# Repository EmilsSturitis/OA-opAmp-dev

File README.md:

# OA-opAmp-dev

 Dev board for OPA2333 with 10 different op amp circuits
 
 Including:
  Non-inverting
  Invering
  Sallen Key filter
  Single to Diff 
  uttt

design has not been tested.

Circuits have been based on the:
https://www.ti.com/lit/ug/sbou193/sbou193.pdf?ts=1656355367396&ref_url=https%253A%252F%252Fwww.ti.com%252Ftool%252FDUAL-DIYAMP-EVM

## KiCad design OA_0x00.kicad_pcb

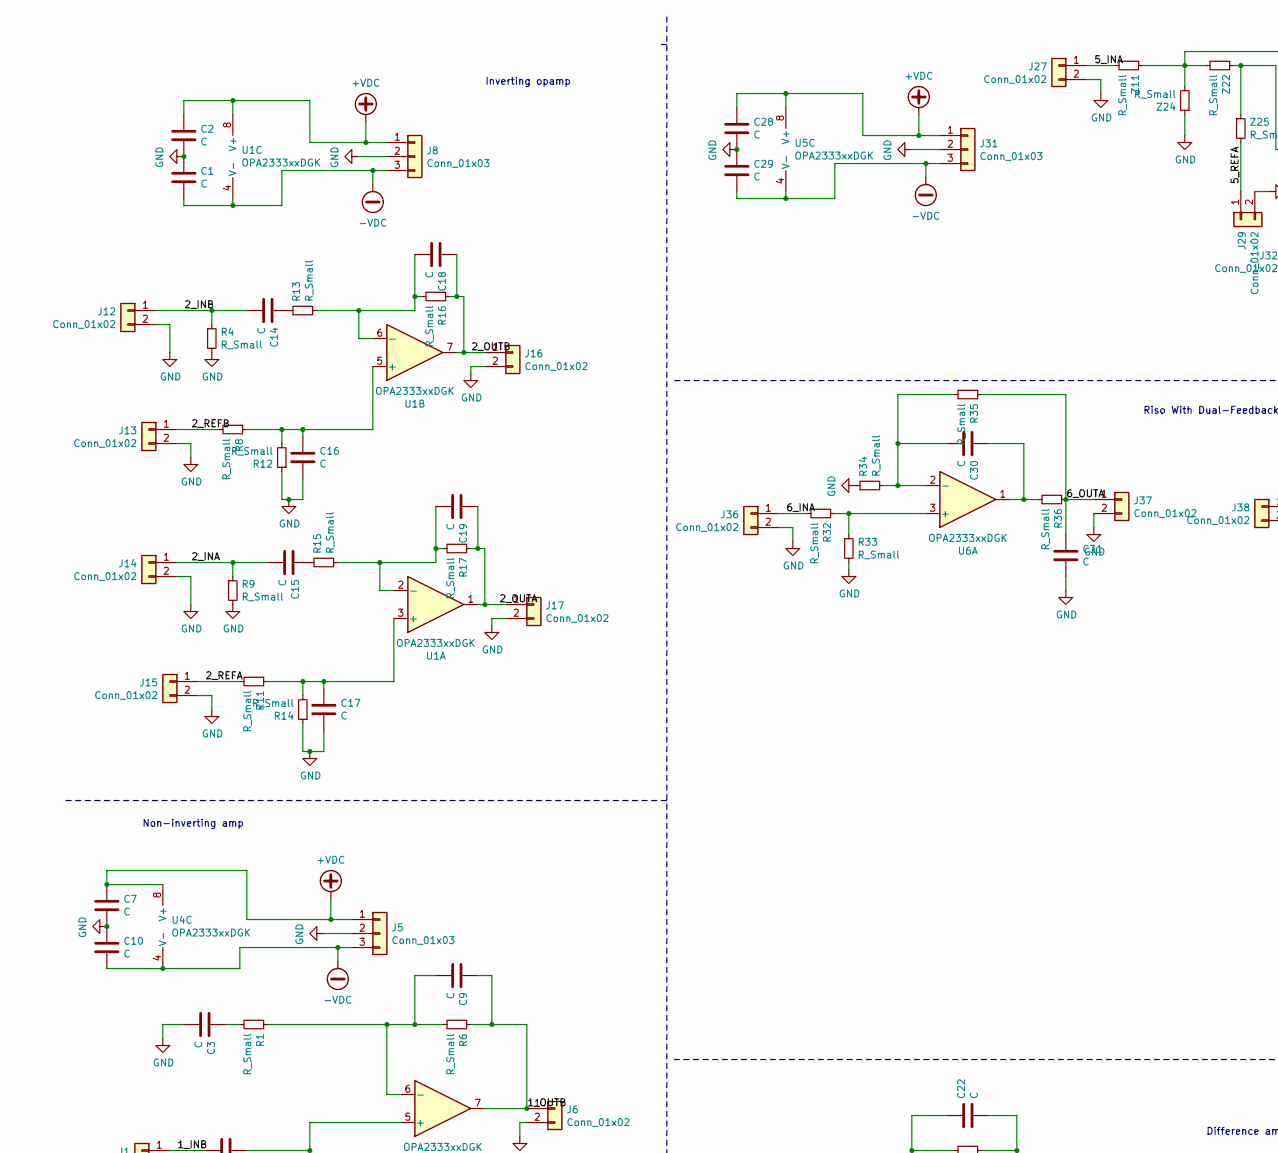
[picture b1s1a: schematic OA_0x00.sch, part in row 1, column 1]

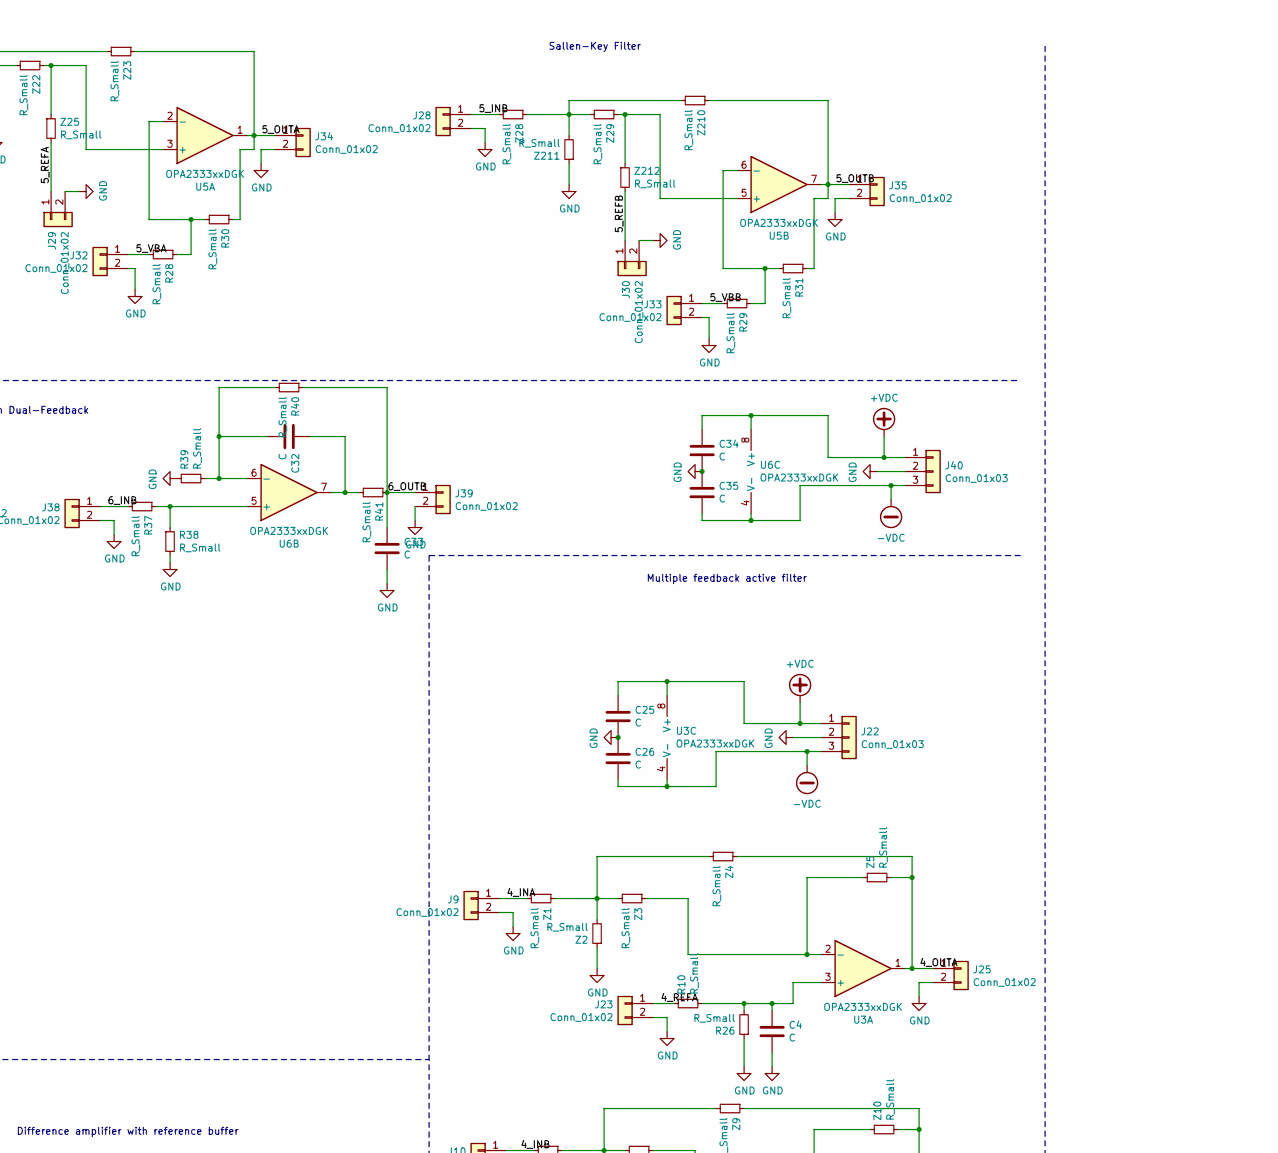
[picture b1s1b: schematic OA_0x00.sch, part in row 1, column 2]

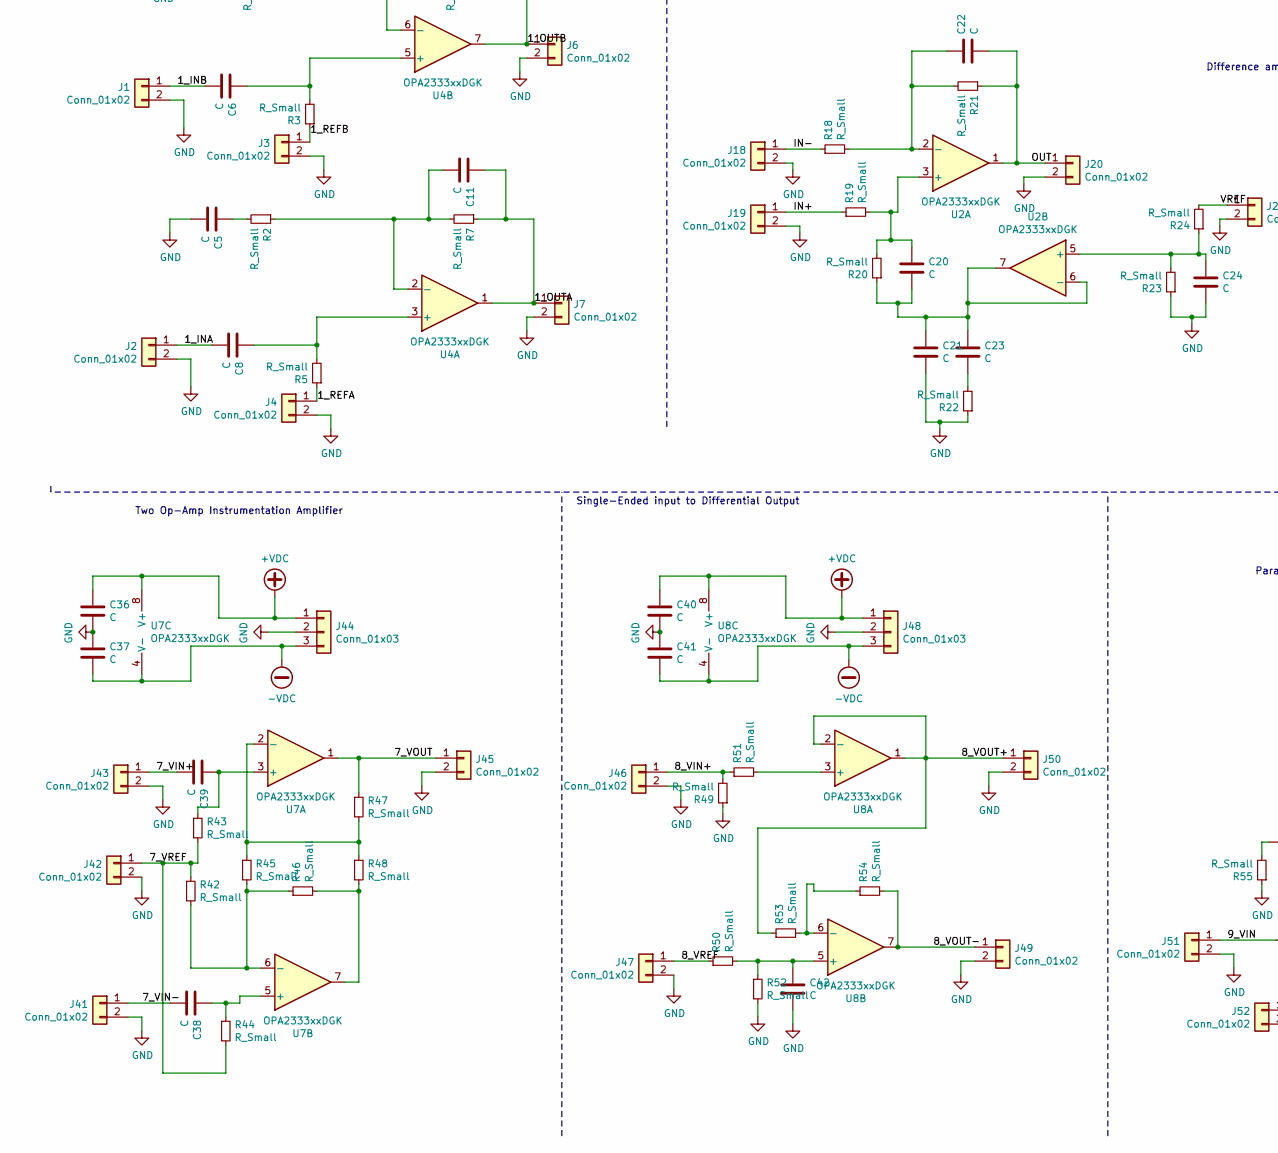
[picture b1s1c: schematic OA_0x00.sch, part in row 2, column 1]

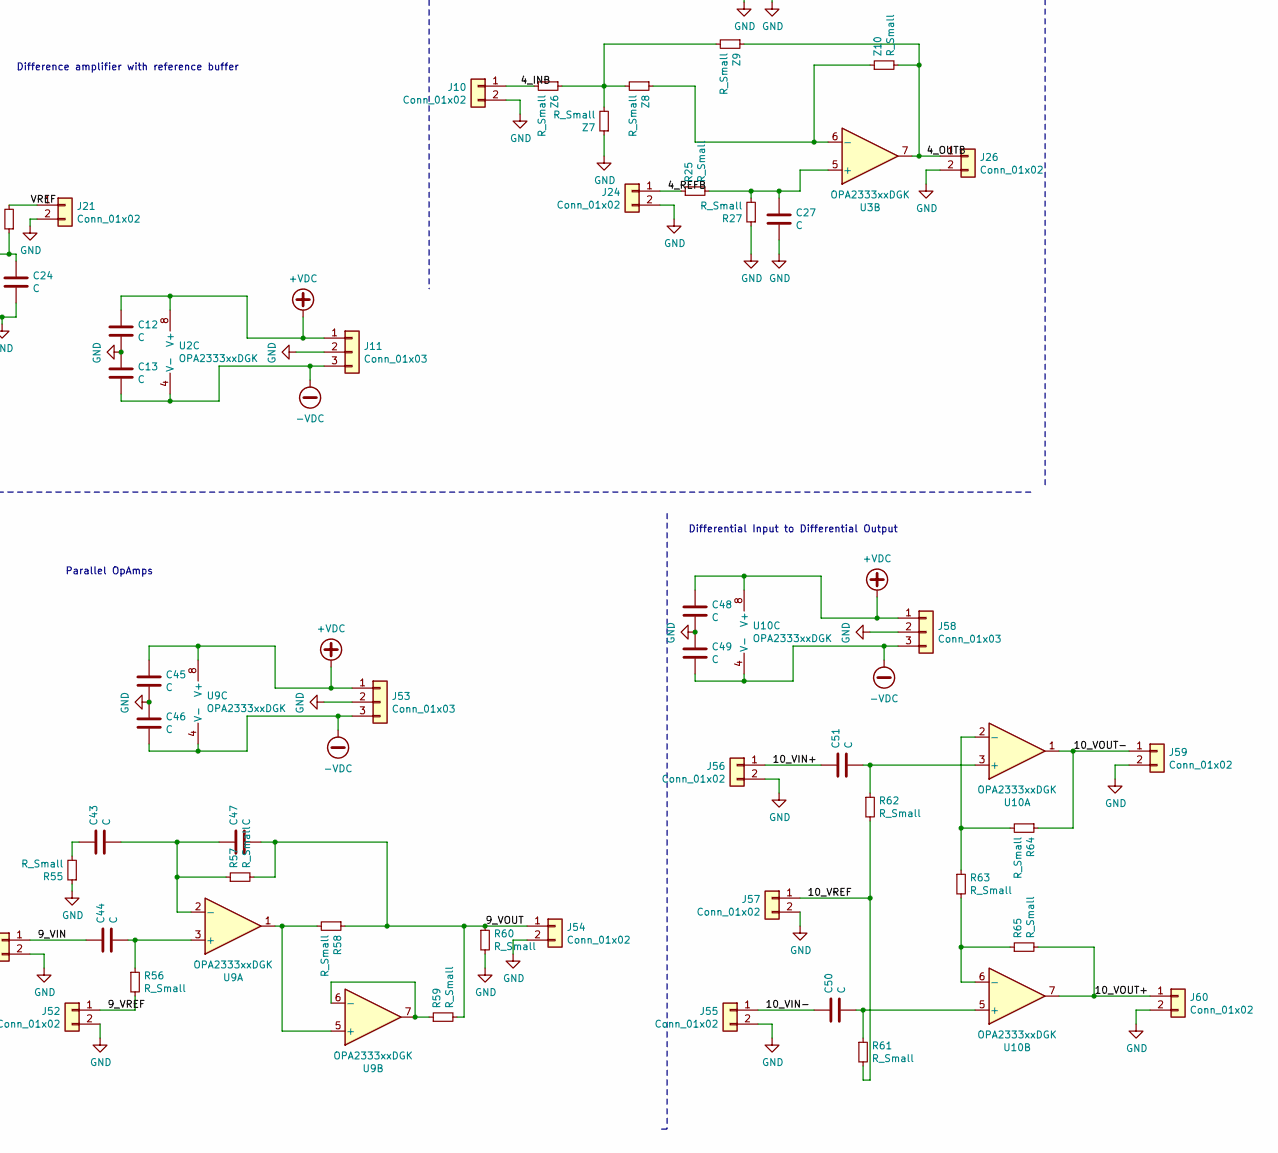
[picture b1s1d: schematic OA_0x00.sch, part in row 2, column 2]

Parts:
C1, C2, C3, C4, C5, C6, C7, C8, C9, C10, C11, C12, C13, C14, C15, C16, C17, C18, C19, C20, C21, C22, C23, C24, C25, C26, C27, C28, C29, C30, C31, C32, C33, C34, C35, C36, C37, C38, C39, C40, C41, C42, C43, C44, C45, C46, C47, C48, C49, C50, C51: C; C_0805_2012Metric_Pad1.18x1.45mm_HandSolder
J1, J2, J3, J4, J6, J7, J9, J10, J12, J13, J14, J15, J16, J17, J18, J19, J20, J21, J23, J24, J25, J26, J27, J28, J29, J30, J32, J33, J34, J35, J36, J37, J38, J39, J41, J42, J43, J45, J46, J47, J49, J50, J51, J52, J54, J55, J56, J57, J59, J60: Conn_01x02; PinHeader_1x02_P2.54mm_Vertical
J5, J8, J11, J22, J31, J40, J44, J48, J53, J58: Conn_01x03; PinHeader_1x03_P2.54mm_Vertical
R1, R2, R3, R4, R5, R6, R7, R8, R9, R10, R11, R12, R13, R14, R15, R16, R17, R18, R19, R20, R21, R22, R23, R24, R25, R26, R27, R28, R29, R30, R31, R32, R33, R34, R35, R36, R37, R38, R39, R40, R41, R42, R43, R44, R45, R46, R47, R48, R49, R50, R51, R52, R53, R54, R55, R56, R57, R58, R59, R60, R61, R62, R63, R64, R65: R_Small; R_0805_2012Metric_Pad1.20x1.40mm_HandSolder
U1, U2, U3, U4, U5, U6, U7, U8, U9, U10: OPA2333xxDGK; VSSOP-8_3.0x3.0mm_P0.65mm
Z1, Z2, Z3, Z4, Z5, Z6, Z7, Z8, Z9, Z10, Z11, Z22, Z23, Z24, Z25, Z28, Z29, Z210, Z211, Z212: R_Small; R_0805_2012Metric_Pad1.20x1.40mm_HandSolder

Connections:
+VDC: C2.1, C7.1, C12.1, C25.1, C28.1, C34.1, C36.1, C40.1, C45.1, C48.1, J5.1, J8.1, J11.1, J22.1, J31.1, J40.1, J44.1, J48.1, J53.1, J58.1, U1.8 (V+), U2.8 (V+), U3.8 (V+), U4.8 (V+), U5.8 (V+), U6.8 (V+), U7.8 (V+), U8.8 (V+), U9.8 (V+), U10.8 (V+)
-VDC: C1.2, C10.2, C13.2, C26.2, C29.2, C35.2, C37.2, C41.2, C46.2, C49.2, J5.3, J8.3, J11.3, J22.3, J31.3, J40.3, J44.3, J48.3, J53.3, J58.3, U1.4 (V-), U2.4 (V-), U3.4 (V-), U4.4 (V-), U5.4 (V-), U6.4 (V-), U7.4 (V-), U8.4 (V-), U9.4 (V-), U10.4 (V-)
/1_INA: C8.2, J2.1
/1_INB: C6.2, J1.1
/1_OUTA: C11.1, J7.1, R7.1, U4.1
/1_OUTB: C9.1, J6.1, R6.1, U4.7
/1_REFA: J4.1, R5.1
/1_REFB: J3.1, R3.1
/2_INA: C15.2, J14.1, R9.1
/2_INB: C14.2, J12.1, R4.1
/2_OUTA: C19.1, J17.1, R17.1, U1.1
/2_OUTB: C18.1, J16.1, R16.1, U1.7
/2_REFA: J15.1, R11.2
/2_REFB: J13.1, R8.2
/4_INA: J9.1, Z1.2
/4_INB: J10.1, Z6.2
/4_OUTA: J25.1, U3.1, Z4.1, Z5.2
/4_OUTB: J26.1, U3.7, Z9.1, Z10.2
/4_REFA: J23.1, R10.1
/4_REFB: J24.1, R25.1
/5_INA: J27.1, Z11.2
/5_INB: J28.1, Z28.2
/5_OUTA: J34.1, R30.1, U5.1, Z23.1
/5_OUTB: J35.1, R31.1, U5.7, Z210.1
/5_REFA: J29.1, Z25.2
/5_REFB: J30.1, Z212.2
/5_VBA: J32.1, R28.2
/5_VBB: J33.1, R29.2
/6_INA: J36.1, R32.2
/6_INB: J38.1, R37.2
/6_OUTA: C31.1, J37.1, R35.1, R36.1
/6_OUTB: C33.1, J39.1, R40.1, R41.1
/7_VIN+: C39.2, J43.1
/7_VIN-: C38.2, J41.1
/7_VOUT: J45.1, R47.1, U7.1
/7_VREF: J42.1, R42.1, R43.2, R44.2
/8_VIN+: J46.1, R49.2, R51.1
/8_VOUT+: J50.1, R53.1, U8.1, U8.2 (-)
/8_VOUT-: J49.1, R54.2, U8.7
/8_VREF: J47.1, R50.1
/9_VIN: C44.1, J51.1
/9_VOUT: C47.2, J54.1, R57.2, R58.1, R59.2, R60.1
/9_VREF: J52.1, R56.2
/10_VIN+: C51.1, J56.1
/10_VIN-: C50.1, J55.1
/10_VOUT+: J60.1, R65.2, U10.7
/10_VOUT-: J59.1, R64.1, U10.1
/10_VREF: J57.1, R61.2, R62.2
/IN+: J19.1, R19.1
/IN-: J18.1, R18.1
/OUT: C22.2, J20.1, R21.1, U2.1
/VREF: J21.1, R24.2
GND: C1.1, C2.2, C3.2, C4.2, C5.2, C7.2, C10.1, C12.2, C13.1, C16.2, C17.2, C21.2, C24.2, C25.2, C26.1, C27.2, C28.2, C29.1, C31.2, C33.2, C34.2, C35.1, C36.2, C37.1, C40.2, C41.1, C42.2, C45.2, C46.1, C48.2, C49.1, J1.2, J2.2, J3.2, J4.2, J5.2, J6.2, J7.2, J8.2, J9.2, J10.2, J11.2, J12.2, J13.2, J14.2, J15.2, J16.2, J17.2, J18.2, J19.2, J20.2, J21.2, J22.2, J23.2, J24.2, J25.2, J26.2, J27.2, J28.2, J29.2, J30.2, J31.2, J32.2, J33.2, J34.2, J35.2, J36.2, J37.2, J38.2, J39.2, J40.2, J41.2, J42.2, J43.2, J44.2, J45.2, J46.2, J47.2, J48.2, J49.2, J50.2, J51.2, J52.2, J53.2, J54.2, J55.2, J56.2, J57.2, J58.2, J59.2, J60.2, R4.2, R9.2, R12.1, R14.1, R22.1, R23.1, R26.1, R27.1, R33.2, R34.1, R38.2, R39.1, R49.1, R52.2, R55.1, R60.2, Z2.1, Z7.1, Z24.1, Z211.1
unnamed: C3.1, R1.2
unnamed: C4.1, R10.2, R26.2, U3.3 (+)
unnamed: C5.1, R2.2
unnamed: C6.1, R3.2, U4.5 (+)
unnamed: C8.1, R5.2, U4.3 (+)
unnamed: C9.2, R1.1, R6.2, U4.6 (-)
unnamed: C11.2, R2.1, R7.2, U4.2 (-)
unnamed: C14.1, R13.1
unnamed: C15.1, R15.1
unnamed: C16.1, R8.1, R12.2, U1.5 (+)
unnamed: C17.1, R11.1, R14.2, U1.3 (+)
unnamed: C18.2, R13.2, R16.2, U1.6 (-)
unnamed: C19.2, R15.2, R17.2, U1.2 (-)
unnamed: C20.1, R19.2, R20.2, U2.3 (+)
unnamed: C20.2, C21.1, C23.1, R20.1, U2.6 (-), U2.7
unnamed: C22.1, R18.2, R21.2, U2.2 (-)
unnamed: C23.2, R22.2
unnamed: C24.1, R23.2, R24.1, U2.5 (+)
unnamed: C27.1, R25.2, R27.2, U3.5 (+)
unnamed: C30.1, R36.2, U6.1
unnamed: C30.2, R34.2, R35.2, U6.2 (-)
unnamed: C32.1, R41.2, U6.7
unnamed: C32.2, R39.2, R40.2, U6.6 (-)
unnamed: C38.1, R44.1, U7.5 (+)
unnamed: C39.1, R43.1, U7.3 (+)
unnamed: C42.1, R50.2, R52.1, U8.5 (+)
unnamed: C43.1, R55.2
unnamed: C43.2, C47.1, R57.1, U9.2 (-)
unnamed: C44.2, R56.1, U9.3 (+)
unnamed: C50.2, R61.1, U10.5 (+)
unnamed: C51.2, R62.1, U10.3 (+)
unnamed: R28.1, R30.2, U5.2 (-)
unnamed: R29.1, R31.2, U5.6 (-)
unnamed: R32.1, R33.1, U6.3 (+)
unnamed: R37.1, R38.1, U6.5 (+)
unnamed: R42.2, R45.2, R46.1, U7.6 (-)
unnamed: R45.1, R47.2, R48.1, U7.2 (-)
unnamed: R46.2, R48.2, U7.7
unnamed: R51.2, U8.3 (+)
unnamed: R53.2, R54.1, U8.6 (-)
unnamed: R58.2, U9.1, U9.5 (+)
unnamed: R59.1, U9.6 (-), U9.7
unnamed: R63.1, R64.2, U10.2 (-)
unnamed: R63.2, R65.1, U10.6 (-)
unnamed: U3.2 (-), Z3.1, Z5.1
unnamed: U3.6 (-), Z8.1, Z10.1
unnamed: U5.3 (+), Z22.1, Z25.1
unnamed: U5.5 (+), Z29.1, Z212.1
unnamed: Z1.1, Z2.2, Z3.2, Z4.2
unnamed: Z6.1, Z7.2, Z8.2, Z9.2
unnamed: Z11.1, Z22.2, Z23.2, Z24.2
unnamed: Z28.1, Z29.2, Z210.2, Z211.2

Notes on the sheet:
Non-inverting amp
Inverting opamp
Difference amplifier with reference buffer
Multiple feedback active filter
Sallen-Key Filter
Riso With Dual-Feedback
Two Op-Amp Instrumentation Amplifier
Single-Ended input to Differential Output
Parallel OpAmps
Differential Input to Differential Output

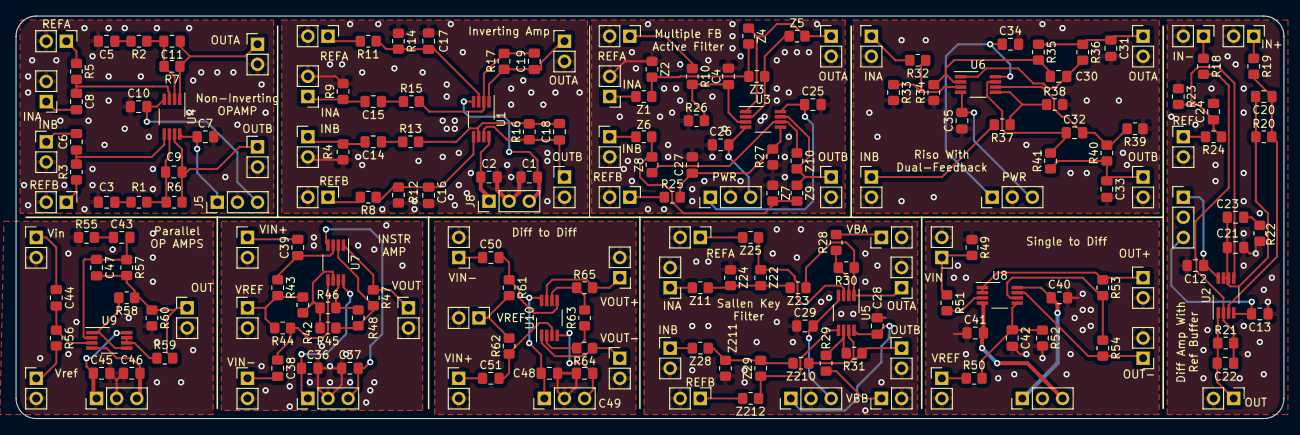
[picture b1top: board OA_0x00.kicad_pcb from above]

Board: 2 copper layers, 160.0 x 50.8 mm, 206 parts (0 on the bottom side), 105 nets.

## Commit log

2022-09-21 begining of calculations for circuits used
